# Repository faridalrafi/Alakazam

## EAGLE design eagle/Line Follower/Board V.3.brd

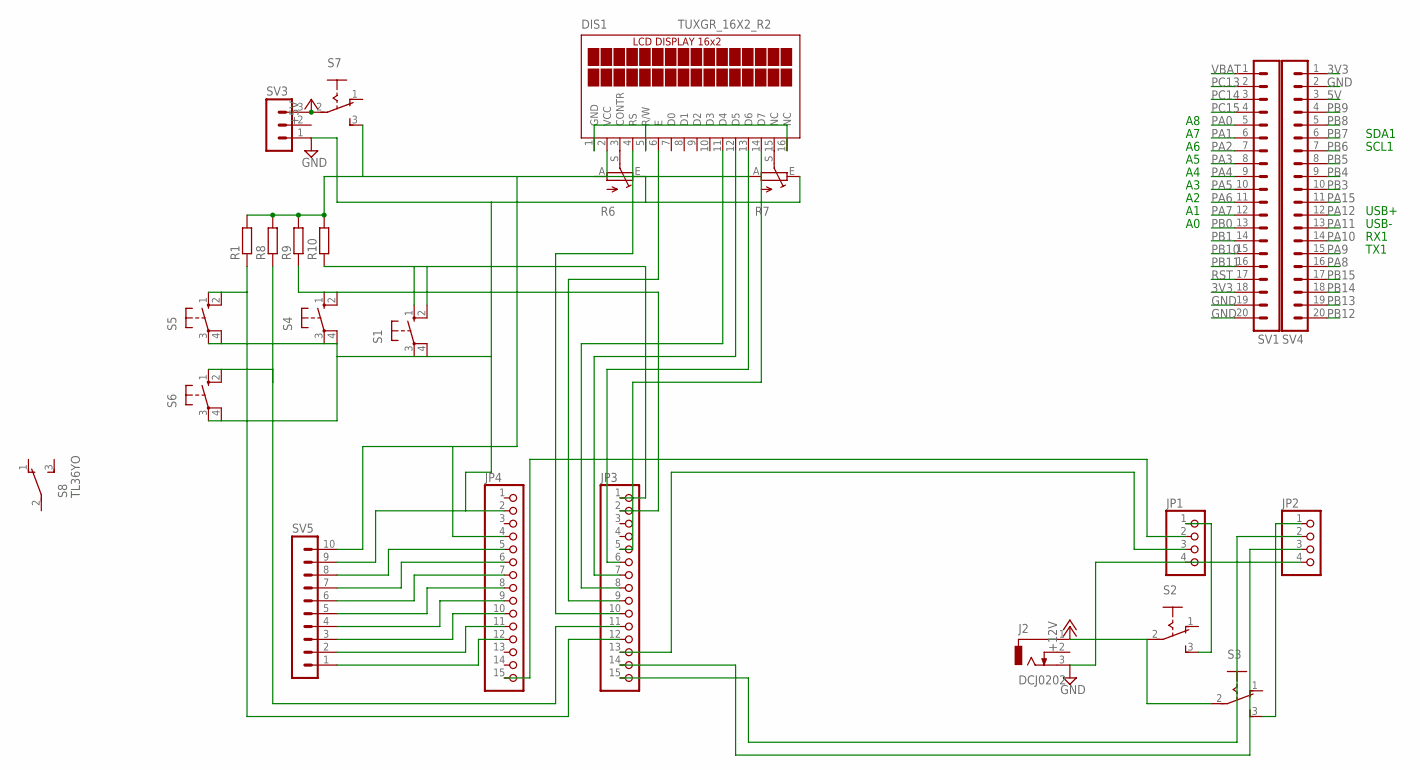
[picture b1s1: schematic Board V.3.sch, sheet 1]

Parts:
DIS1: TUXGR_16X2_R2
J2: DCJ0202
JP1, JP2: PINHD-1X4; 1X04
JP3, JP4: PINHD-1X15; 1X15
R1, R8, R9, R10: R-EU_0204/7; 0204/7
R6, R7: TRIM_EU-B25P; B25P
S1, S4, S5, S6: 10-XX; B3F-10XX
S2, S3, S7: 255SB
S8: TL36YO; TL3XYO
SV1, SV4: MA20-1L
SV3: MA03-1
SV5: MA10-1

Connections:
3V3: SV1.18, SV4.1
5V: SV4.3
+5V: S7.2, SV3.3
+5V2: DIS1.2 (VCC), JP4.4, R1.2, R6.A, R7.A, R8.2, R9.2, R10.2, S7.3 (S), SV5.10
+12V: J2.1, S2.2, S3.2
GND: J2.3, JP1.4, JP2.4, JP4.2, R6.E, R7.E, S1.3, S1.4 (P1), S4.3, S4.4 (P1), S5.3, S5.4 (P1), S6.3, S6.4 (P1), SV1.19, SV1.20, SV3.1, SV4.2, SV5.9
unnamed: JP1.1, S2.3 (S)
unnamed: JP2.1, S3.3 (S)
unnamed: JP3.1, R10.1, S1.1 (S), S1.2 (S1)
unnamed: DIS1.15 (NC), R7.S
unnamed: DIS1.4 (RS), JP3.10
unnamed: DIS1.3 (CONTR), R6.S
unnamed: DIS1.6 (E), JP3.9
unnamed: DIS1.11 (D4), JP3.8
unnamed: JP4.5, SV5.8
unnamed: JP4.6, SV5.7
unnamed: JP4.7, SV5.6
unnamed: JP4.8, SV5.5
unnamed: JP4.9, SV5.4
unnamed: DIS1.12 (D5), JP3.7
unnamed: DIS1.13 (D6), JP3.6
unnamed: DIS1.14 (D7), JP3.5
unnamed: JP3.2, R9.1, S4.1 (S), S4.2 (S1)
unnamed: JP3.11, R8.1, S6.1 (S), S6.2 (S1)
unnamed: JP3.12, R1.1, S5.1 (S), S5.2 (S1)
unnamed: DIS1.1 (GND), DIS1.5 (R/W), DIS1.16 (NC)
unnamed: JP2.3, JP3.14
unnamed: JP4.10, SV5.3
unnamed: JP4.11, SV5.2
unnamed: JP4.12, SV5.1
PA0: SV1.5
PA1: SV1.6
PA2: SV1.7
PA3: SV1.8
PA4: SV1.9
PA5: SV1.10
PA6: SV1.11
PA7: SV1.12
PA8: SV4.16
PA9: SV4.15
PA10: SV4.14
PA11: SV4.13
PA12: SV4.12
PA15: SV4.11
PB0: SV1.13
PB1: SV1.14
PB3: SV4.10
PB4: SV4.9
PB5: SV4.8
PB6: SV4.7
PB7: SV4.6
PB8: SV4.5
PB9: SV4.4
PB10: SV1.15
PB11: SV1.16
PB12: SV4.20
PB13: SV4.19
PB14: SV4.18
PB15: SV4.17
PC13: SV1.2
PC14: SV1.3
PC15: SV1.4
RST: SV1.17
VBAT: SV1.1

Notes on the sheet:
SDA1
SCL1
RX1
TX1
USB-
USB+

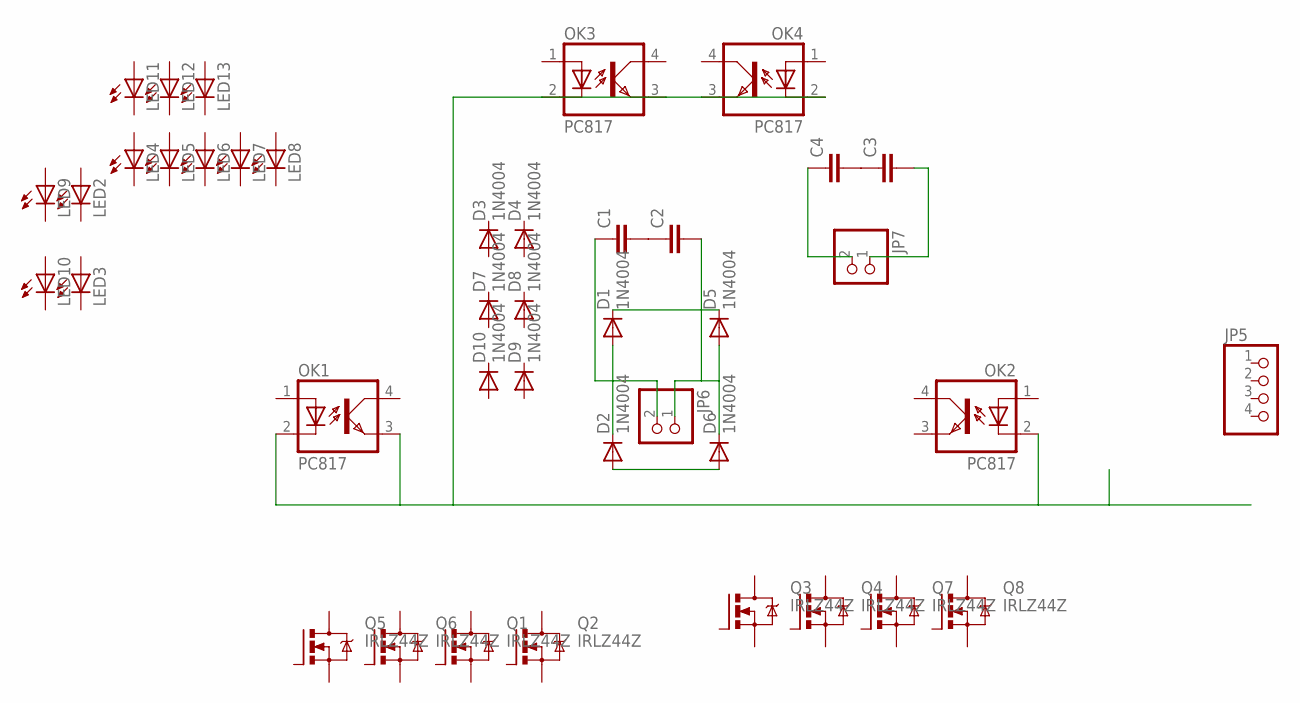
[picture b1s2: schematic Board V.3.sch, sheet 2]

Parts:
C1, C2, C3, C4: C-EU025-025X050; C025-025X050
D1, D2, D3, D4, D5, D6, D7, D8, D9, D10: 1N4004; DO41-10
JP5: PINHD-1X4; 1X04
JP6, JP7: PINHD-1X2/90; 1X02/90
LED2, LED3, LED4, LED5, LED6, LED7, LED8, LED9, LED10, LED11, LED12, LED13: LED5MM
OK1, OK2, OK3, OK4: PC817; DIL04
Q1, Q2, Q3, Q4, Q5, Q6, Q7, Q8: IRLZ44Z; TO220BH

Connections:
+12V1: D1.C, D5.C
GND1: OK1.2 (C), OK1.3 (EMIT), OK2.2 (C), OK3.2 (C), OK3.3 (EMIT), OK4.2 (C), OK4.3 (EMIT)
unnamed: C3.1, C4.2
unnamed: D2.A, D6.A
unnamed: C4.1, JP7.2
unnamed: C1.2, C2.1
unnamed: C1.1, D1.A, D2.C, JP6.2
unnamed: C3.2, JP7.1
unnamed: C2.2, D5.A, D6.C, JP6.1

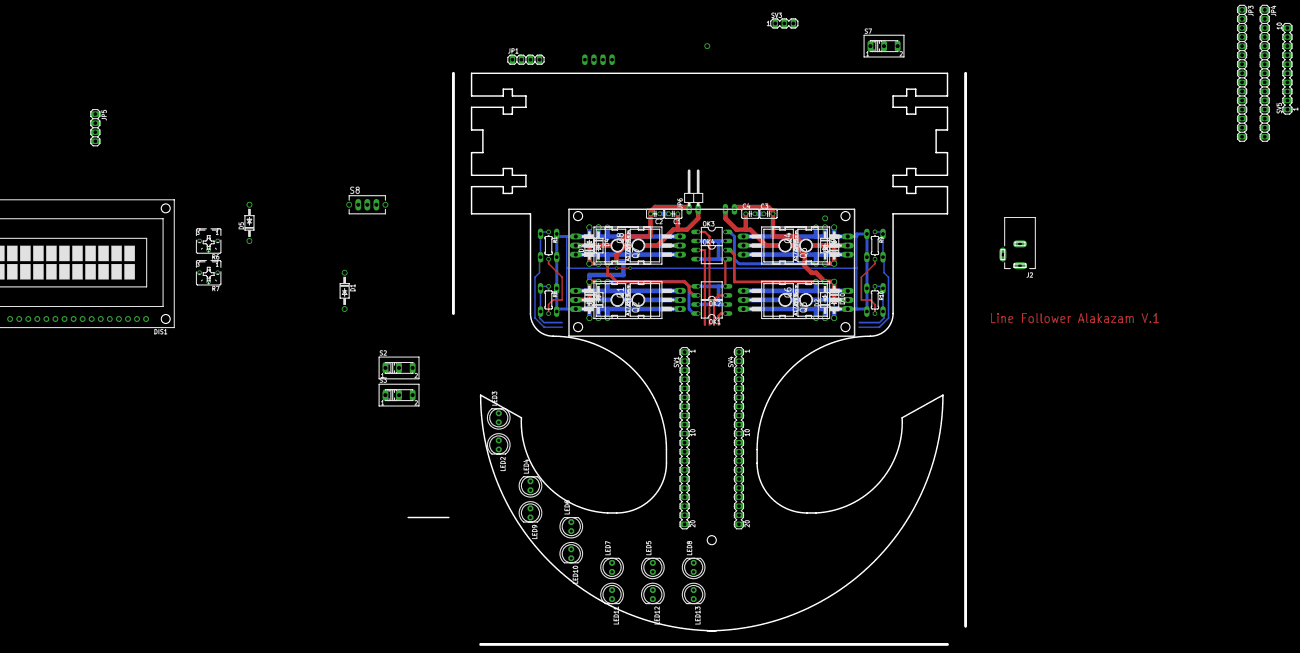
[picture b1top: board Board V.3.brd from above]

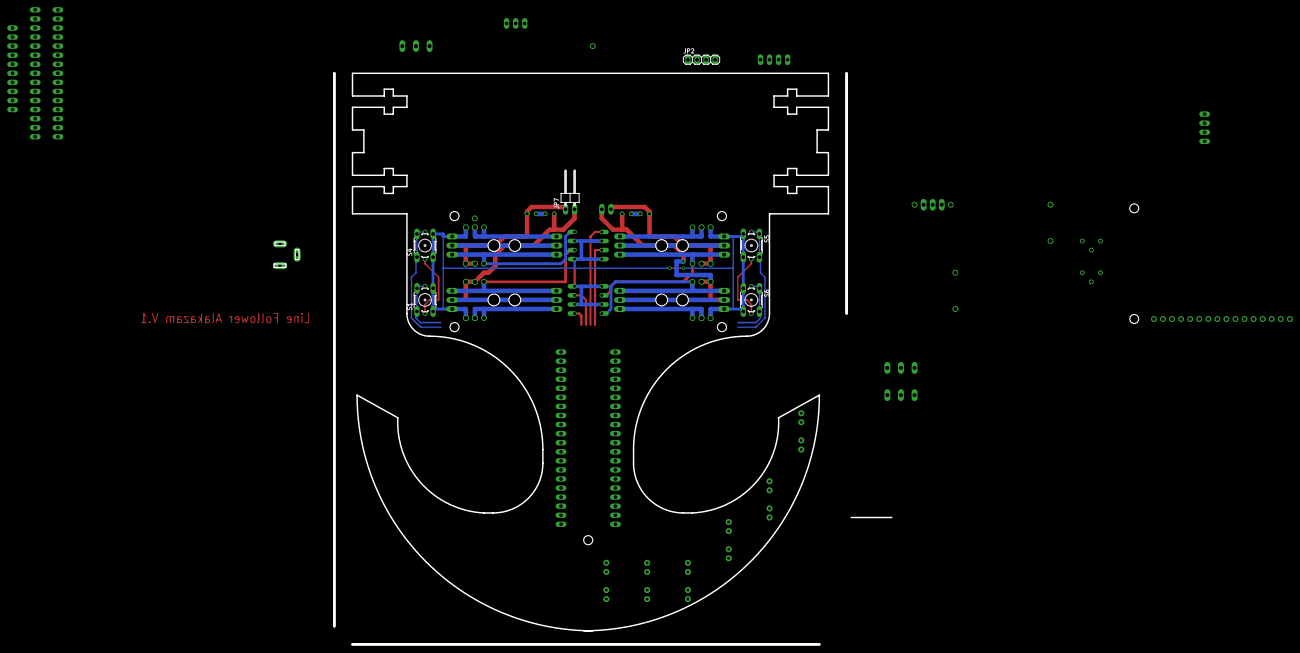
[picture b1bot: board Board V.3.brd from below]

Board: 2 copper layers, 173.1 x 160.0 mm, 65 parts (6 on the bottom side), 38 nets.

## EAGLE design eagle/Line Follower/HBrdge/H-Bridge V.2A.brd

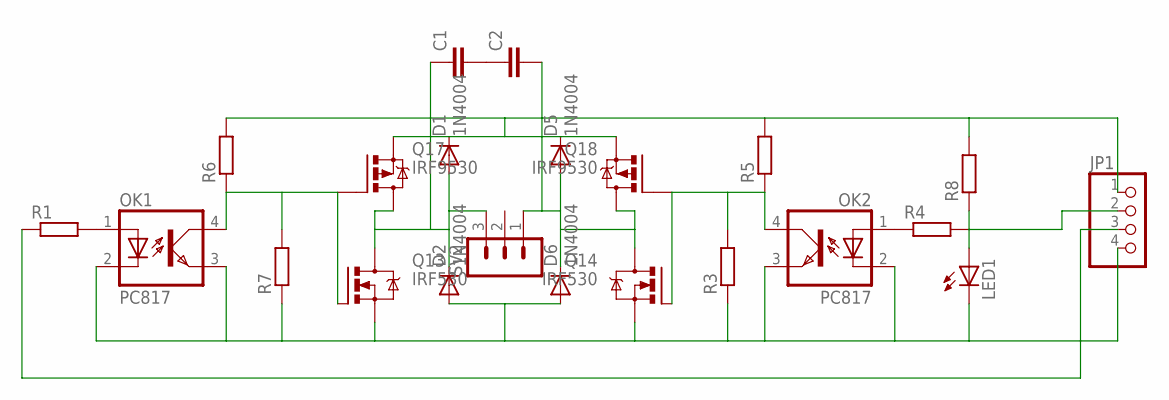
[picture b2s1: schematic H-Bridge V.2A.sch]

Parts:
C1, C2: C-EU025-025X050; C025-025X050
D1, D2, D5, D6: 1N4004; DO41-10
JP1: PINHD-1X4; 1X04
LED1: LED3MM
OK1, OK2: PC817; DIL04
Q13, Q14: IRF530; TO220BV
Q17, Q18: IRF9530; TO220BV
R1, R4, R5, R6, R8: R-EU_0207/10; 0207/10
R3, R7: R-EU_0204/7; 0204/7
SV2: MA03-1

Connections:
+12V: D1.C, D5.C, JP1.1, Q17.S, Q18.S, R5.2, R6.2, R8.2
GND: D2.A, D6.A, JP1.4, LED1.K (C), OK1.2 (C), OK1.3 (EMIT), OK2.2 (C), OK2.3 (EMIT), Q13.S, Q14.S, R3.1, R7.1
unnamed: OK2.1 (A), R4.1
unnamed: OK1.1 (A), R1.2
unnamed: C1.2, C2.1
unnamed: C2.2, D5.A, D6.C, Q14.D, Q18.D, SV2.1
unnamed: C1.1, D1.A, D2.C, Q13.D, Q17.D, SV2.3
unnamed: LED1.A, R8.1
unnamed: OK2.4 (COL), Q14.G, Q18.G, R3.2, R5.1
unnamed: OK1.4 (COL), Q13.G, Q17.G, R6.1, R7.2
PWM1: JP1.2, R4.2
PWM2: JP1.3, R1.1

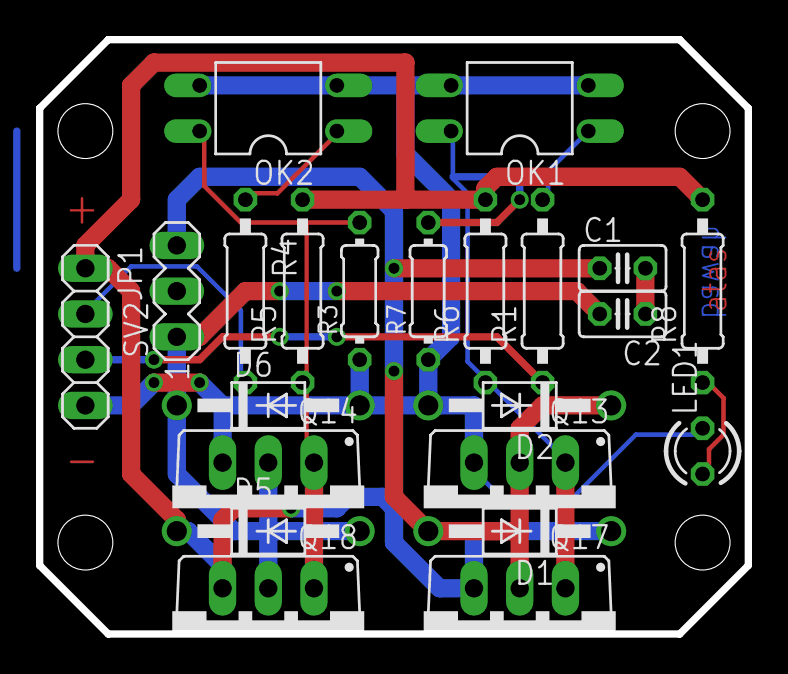
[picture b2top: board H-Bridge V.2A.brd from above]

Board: 2 copper layers, 39.4 x 33.0 mm, 22 parts (0 on the bottom side), 12 nets.

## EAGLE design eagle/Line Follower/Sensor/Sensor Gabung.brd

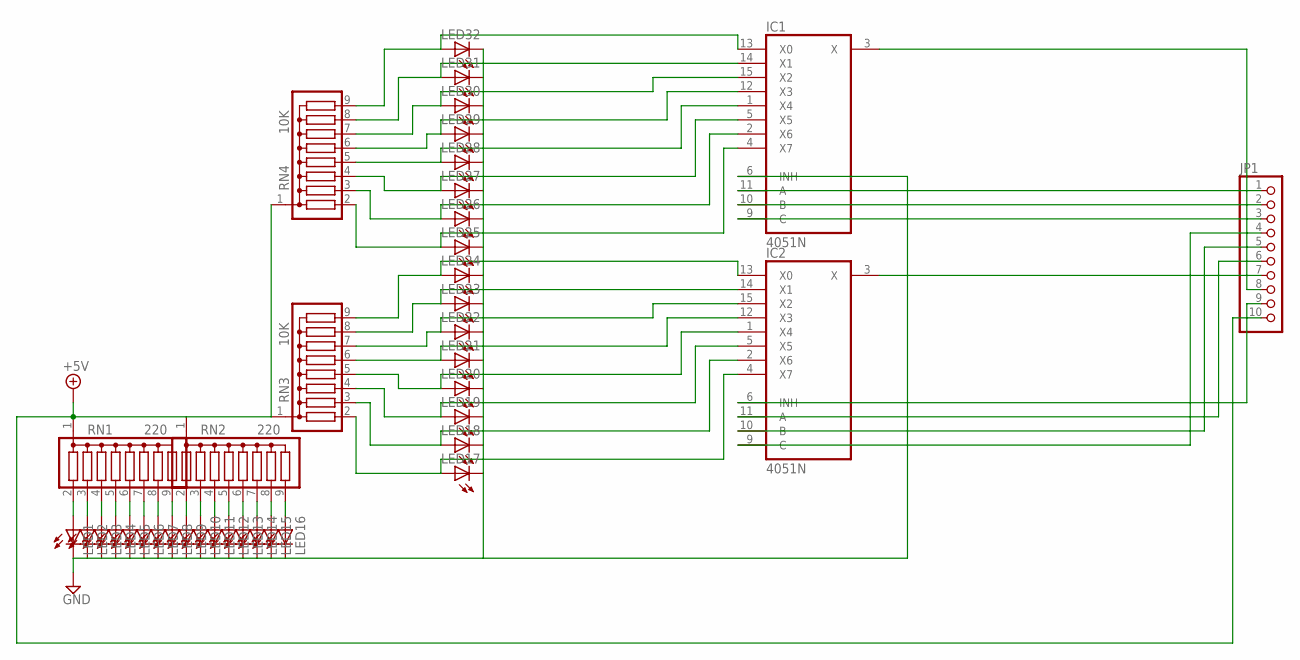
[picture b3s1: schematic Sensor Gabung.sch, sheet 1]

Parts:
IC1, IC2: 4051N; DIL16
JP1: PINHD-1X10; 1X10
LED1, LED2, LED3, LED4, LED5, LED6, LED7, LED8, LED9, LED10, LED11, LED12, LED13, LED14, LED15, LED16, LED17, LED18, LED19, LED20, LED21, LED22, LED23, LED24, LED25, LED26, LED27, LED28, LED29, LED30, LED31, LED32: LED3MM
RN1, RN2: 220; SIL9
RN3, RN4: 10K; SIL9

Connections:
+5V: IC1.16 (VCC), IC2.16 (VCC), JP1.10, RN1.1, RN2.1, RN3.1, RN4.1; also elsewhere on the board
GND: IC1.6 (INH), IC1.8 (GND), IC2.6 (INH), IC2.8 (GND), JP1.9, LED1.K (C), LED2.K (C), LED3.K (C), LED4.K (C), LED5.K (C), LED6.K (C), LED7.K (C), LED8.K (C), LED9.K (C), LED10.K (C), LED11.K (C), LED12.K (C), LED13.K (C), LED14.K (C), LED15.K (C), LED16.K (C), LED17.K (C), LED18.K (C), LED19.K (C), LED20.K (C), LED21.K (C), LED22.K (C), LED23.K (C), LED24.K (C), LED25.K (C), LED26.K (C), LED27.K (C), LED28.K (C), LED29.K (C), LED30.K (C), LED31.K (C), LED32.K (C); also elsewhere on the board
unnamed: IC1.10 (B), JP1.2
unnamed: IC1.9 (C), JP1.3
unnamed: IC2.11 (A), JP1.6
unnamed: IC2.10 (B), JP1.5
unnamed: IC2.9 (C), JP1.4
unnamed: IC2.3 (X), JP1.7
unnamed: LED1.A, RN1.2
unnamed: LED2.A, RN1.3
unnamed: IC2.4 (X7), LED17.A, RN3.2
unnamed: IC2.2 (X6), LED18.A, RN3.3
unnamed: IC2.5 (X5), LED19.A, RN3.4
unnamed: IC2.1 (X4), LED20.A, RN3.5
unnamed: IC2.12 (X3), LED21.A, RN3.6
unnamed: IC2.15 (X2), LED22.A, RN3.7
unnamed: IC2.14 (X1), LED23.A, RN3.8
unnamed: IC2.13 (X0), LED24.A, RN3.9
unnamed: IC1.4 (X7), LED25.A, RN4.2
unnamed: IC1.2 (X6), LED26.A, RN4.3
unnamed: IC1.5 (X5), LED27.A, RN4.4
unnamed: IC1.1 (X4), LED28.A, RN4.5
unnamed: IC1.12 (X3), LED29.A, RN4.6
unnamed: IC1.15 (X2), LED30.A, RN4.7
unnamed: IC1.14 (X1), LED31.A, RN4.8
unnamed: IC1.13 (X0), LED32.A, RN4.9
unnamed: LED3.A, RN1.4
unnamed: LED4.A, RN1.5
unnamed: LED5.A, RN1.6
unnamed: LED6.A, RN1.7
unnamed: LED7.A, RN1.8
unnamed: LED8.A, RN1.9
unnamed: LED9.A, RN2.2
unnamed: LED10.A, RN2.3
unnamed: LED11.A, RN2.4
unnamed: LED12.A, RN2.5
unnamed: LED13.A, RN2.6
unnamed: LED14.A, RN2.7
unnamed: LED15.A, RN2.8
unnamed: LED16.A, RN2.9
unnamed: IC1.3 (X), JP1.8
unnamed: IC1.11 (A), JP1.1
VEE: IC1.7 (VEE), IC2.7 (VEE)

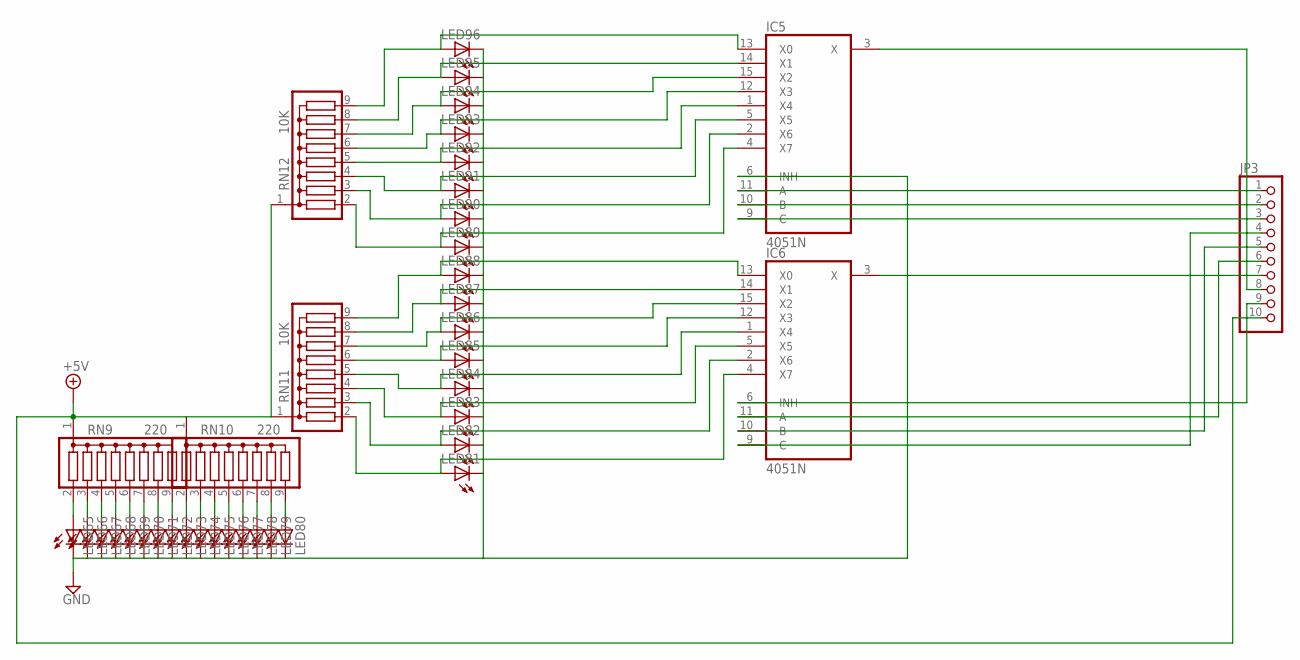
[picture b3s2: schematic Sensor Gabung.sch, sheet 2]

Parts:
IC5, IC6: 4051N; DIL16
JP3: PINHD-1X10; 1X10
LED65, LED66, LED67, LED68, LED69, LED70, LED71, LED72, LED73, LED74, LED75, LED76, LED77, LED78, LED79, LED80, LED81, LED82, LED83, LED84, LED85, LED86, LED87, LED88, LED89, LED90, LED91, LED92, LED93, LED94, LED95, LED96: LED3MM
RN9, RN10: 220; SIL9
RN11, RN12: 10K; SIL9

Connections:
+5V: IC5.16 (VCC), IC6.16 (VCC), JP3.10, RN9.1, RN10.1, RN11.1, RN12.1; also elsewhere on the board
GND: IC5.6 (INH), IC5.7 (VEE), IC5.8 (GND), IC6.6 (INH), IC6.7 (VEE), IC6.8 (GND), JP3.9, LED65.K (C), LED66.K (C), LED67.K (C), LED68.K (C), LED69.K (C), LED70.K (C), LED71.K (C), LED72.K (C), LED73.K (C), LED74.K (C), LED75.K (C), LED76.K (C), LED77.K (C), LED78.K (C), LED79.K (C), LED80.K (C), LED81.K (C), LED82.K (C), LED83.K (C), LED84.K (C), LED85.K (C), LED86.K (C), LED87.K (C), LED88.K (C), LED89.K (C), LED90.K (C), LED91.K (C), LED92.K (C), LED93.K (C), LED94.K (C), LED95.K (C), LED96.K (C); also elsewhere on the board
unnamed: IC6.4 (X7), LED81.A, RN11.2
unnamed: IC6.2 (X6), LED82.A, RN11.3
unnamed: IC6.5 (X5), LED83.A, RN11.4
unnamed: IC6.1 (X4), LED84.A, RN11.5
unnamed: IC6.12 (X3), LED85.A, RN11.6
unnamed: IC6.15 (X2), LED86.A, RN11.7
unnamed: IC6.14 (X1), LED87.A, RN11.8
unnamed: IC6.13 (X0), LED88.A, RN11.9
unnamed: IC5.4 (X7), LED89.A, RN12.2
unnamed: IC5.2 (X6), LED90.A, RN12.3
unnamed: IC5.5 (X5), LED91.A, RN12.4
unnamed: IC5.1 (X4), LED92.A, RN12.5
unnamed: IC5.12 (X3), LED93.A, RN12.6
unnamed: IC5.15 (X2), LED94.A, RN12.7
unnamed: IC5.14 (X1), LED95.A, RN12.8
unnamed: IC5.13 (X0), LED96.A, RN12.9
unnamed: LED65.A, RN9.2
unnamed: LED66.A, RN9.3
unnamed: LED67.A, RN9.4
unnamed: LED68.A, RN9.5
unnamed: LED69.A, RN9.6
unnamed: LED70.A, RN9.7
unnamed: LED71.A, RN9.8
unnamed: LED72.A, RN9.9
unnamed: LED73.A, RN10.2
unnamed: LED74.A, RN10.3
unnamed: LED75.A, RN10.4
unnamed: LED76.A, RN10.5
unnamed: LED77.A, RN10.6
unnamed: LED78.A, RN10.7
unnamed: LED79.A, RN10.8
unnamed: LED80.A, RN10.9
unnamed: IC5.3 (X), JP3.8
unnamed: IC5.11 (A), JP3.1
unnamed: IC5.10 (B), JP3.2
unnamed: IC5.9 (C), JP3.3
unnamed: IC6.11 (A), JP3.6
unnamed: IC6.10 (B), JP3.5
unnamed: IC6.9 (C), JP3.4
unnamed: IC6.3 (X), JP3.7

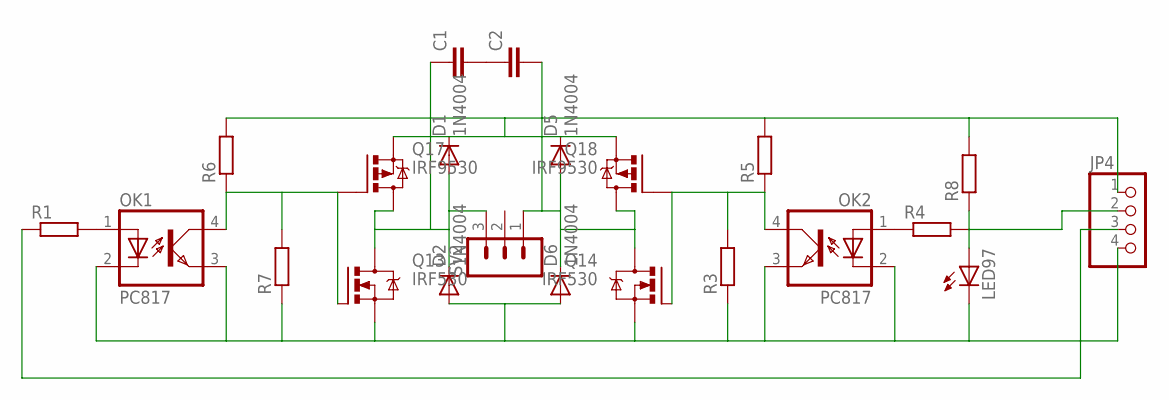
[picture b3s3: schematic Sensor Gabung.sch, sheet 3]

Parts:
C1, C2: C-EU025-025X050; C025-025X050
D1, D2, D5, D6: 1N4004; DO41-10
JP4: PINHD-1X4; 1X04
LED97: LED3MM
OK1, OK2: PC817; DIL04
Q13, Q14: IRF530; TO220BV
Q17, Q18: IRF9530; TO220BV
R1, R4, R5, R6, R8: R-EU_0207/10; 0207/10
R3, R7: R-EU_0204/7; 0204/7
SV2: MA03-1

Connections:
+12V: D1.C, D5.C, JP4.1, Q17.S, Q18.S, R5.2, R6.2, R8.2
GND1: D2.A, D6.A, JP4.4, LED97.K (C), OK1.2 (C), OK1.3 (EMIT), OK2.2 (C), OK2.3 (EMIT), Q13.S, Q14.S, R3.1, R7.1; also elsewhere on the board
unnamed: C2.2, D5.A, D6.C, Q14.D, Q18.D, SV2.1
unnamed: C1.1, D1.A, D2.C, Q13.D, Q17.D, SV2.3
unnamed: OK2.4 (COL), Q14.G, Q18.G, R3.2, R5.1
unnamed: OK1.4 (COL), Q13.G, Q17.G, R6.1, R7.2
unnamed: LED97.A, R8.1
unnamed: OK2.1 (A), R4.1
unnamed: OK1.1 (A), R1.2
unnamed: C1.2, C2.1
PWM1: JP4.2, R4.2
PWM2: JP4.3, R1.1

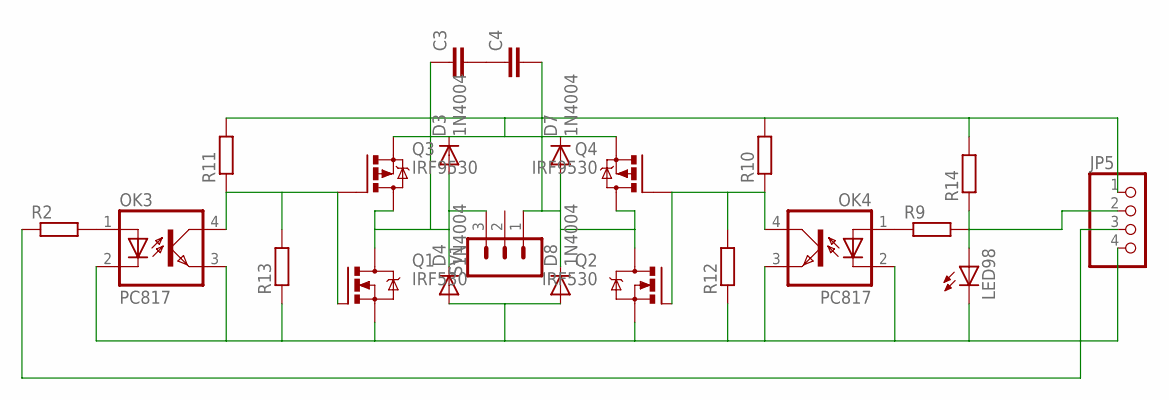
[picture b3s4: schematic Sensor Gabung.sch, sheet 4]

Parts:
C3, C4: C-EU025-025X050; C025-025X050
D3, D4, D7, D8: 1N4004; DO41-10
JP5: PINHD-1X4; 1X04
LED98: LED3MM
OK3, OK4: PC817; DIL04
Q1, Q2: IRF530; TO220BV
Q3, Q4: IRF9530; TO220BV
R2, R9, R10, R11, R14: R-EU_0207/10; 0207/10
R12, R13: R-EU_0204/7; 0204/7
SV1: MA03-1

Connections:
+12V1: D3.C, D7.C, JP5.1, Q3.S, Q4.S, R10.2, R11.2, R14.2
GND2: D4.A, D8.A, JP5.4, LED98.K (C), OK3.2 (C), OK3.3 (EMIT), OK4.2 (C), OK4.3 (EMIT), Q1.S, Q2.S, R12.1, R13.1
unnamed: C4.2, D7.A, D8.C, Q2.D, Q4.D, SV1.1
unnamed: C3.1, D3.A, D4.C, Q1.D, Q3.D, SV1.3
unnamed: OK4.4 (COL), Q2.G, Q4.G, R10.1, R12.2
unnamed: OK3.4 (COL), Q1.G, Q3.G, R11.1, R13.2
unnamed: LED98.A, R14.1
unnamed: OK4.1 (A), R9.1
unnamed: OK3.1 (A), R2.2
unnamed: C3.2, C4.1
PWM3: JP5.3, R2.1
PWM4: JP5.2, R9.2

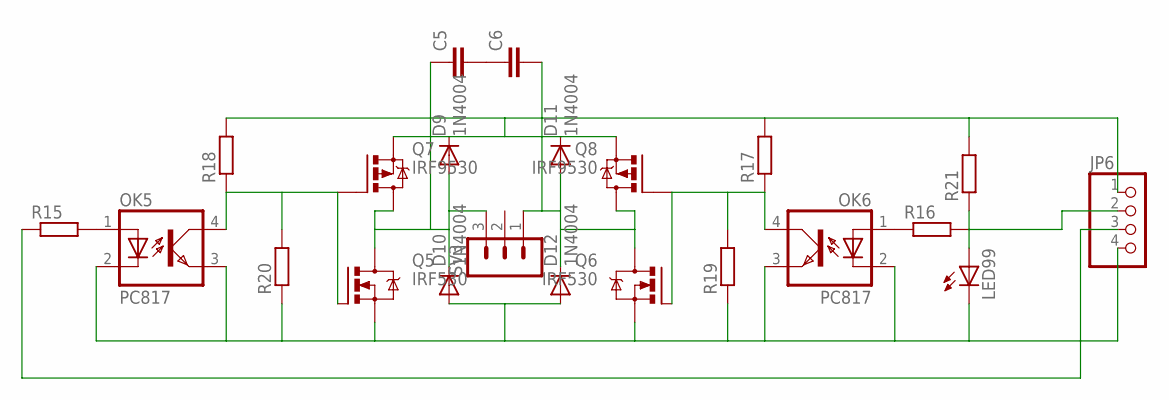
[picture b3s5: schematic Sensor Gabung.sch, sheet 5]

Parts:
C5, C6: C-EU025-025X050; C025-025X050
D9, D10, D11, D12: 1N4004; DO41-10
JP6: PINHD-1X4; 1X04
LED99: LED3MM
OK5, OK6: PC817; DIL04
Q5, Q6: IRF530; TO220BV
Q7, Q8: IRF9530; TO220BV
R15, R16, R17, R18, R21: R-EU_0207/10; 0207/10
R19, R20: R-EU_0204/7; 0204/7
SV3: MA03-1

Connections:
+12V2: D9.C, D11.C, JP6.1, Q7.S, Q8.S, R17.2, R18.2, R21.2
GND3: D10.A, D12.A, JP6.4, LED99.K (C), OK5.2 (C), OK5.3 (EMIT), OK6.2 (C), OK6.3 (EMIT), Q5.S, Q6.S, R19.1, R20.1
unnamed: C6.2, D11.A, D12.C, Q6.D, Q8.D, SV3.1
unnamed: C5.1, D9.A, D10.C, Q5.D, Q7.D, SV3.3
unnamed: OK6.4 (COL), Q6.G, Q8.G, R17.1, R19.2
unnamed: OK5.4 (COL), Q5.G, Q7.G, R18.1, R20.2
unnamed: LED99.A, R21.1
unnamed: OK6.1 (A), R16.1
unnamed: OK5.1 (A), R15.2
unnamed: C5.2, C6.1
PWM5: JP6.3, R15.1
PWM6: JP6.2, R16.2

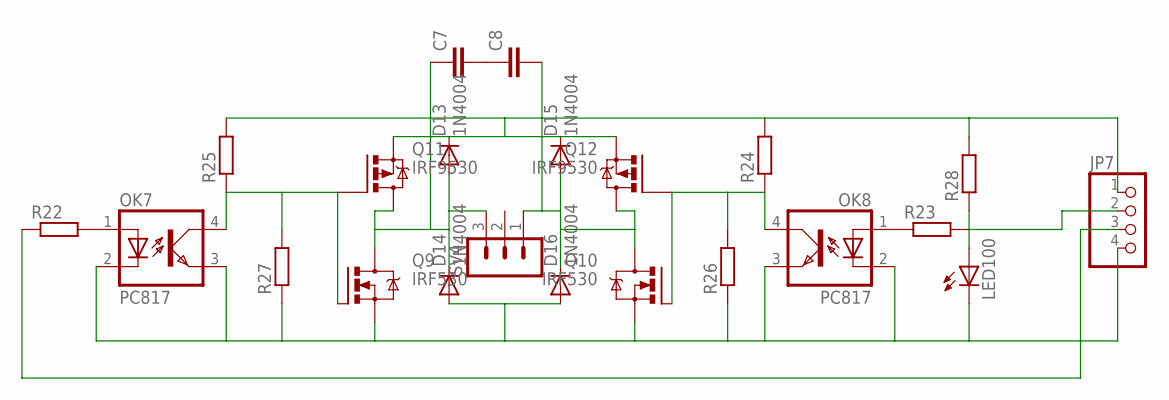
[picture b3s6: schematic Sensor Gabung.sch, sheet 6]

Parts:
C7, C8: C-EU025-025X050; C025-025X050
D13, D14, D15, D16: 1N4004; DO41-10
JP7: PINHD-1X4; 1X04
LED100: LED3MM
OK7, OK8: PC817; DIL04
Q9, Q10: IRF530; TO220BV
Q11, Q12: IRF9530; TO220BV
R22, R23, R24, R25, R28: R-EU_0207/10; 0207/10
R26, R27: R-EU_0204/7; 0204/7
SV4: MA03-1

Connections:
+12V3: D13.C, D15.C, JP7.1, Q11.S, Q12.S, R24.2, R25.2, R28.2
GND4: D14.A, D16.A, JP7.4, LED100.K (C), OK7.2 (C), OK7.3 (EMIT), OK8.2 (C), OK8.3 (EMIT), Q9.S, Q10.S, R26.1, R27.1
unnamed: C8.2, D15.A, D16.C, Q10.D, Q12.D, SV4.1
unnamed: C7.1, D13.A, D14.C, Q9.D, Q11.D, SV4.3
unnamed: OK8.4 (COL), Q10.G, Q12.G, R24.1, R26.2
unnamed: OK7.4 (COL), Q9.G, Q11.G, R25.1, R27.2
unnamed: LED100.A, R28.1
unnamed: OK8.1 (A), R23.1
unnamed: OK7.1 (A), R22.2
unnamed: C7.2, C8.1
PWM7: JP7.3, R22.1
PWM8: JP7.2, R23.2

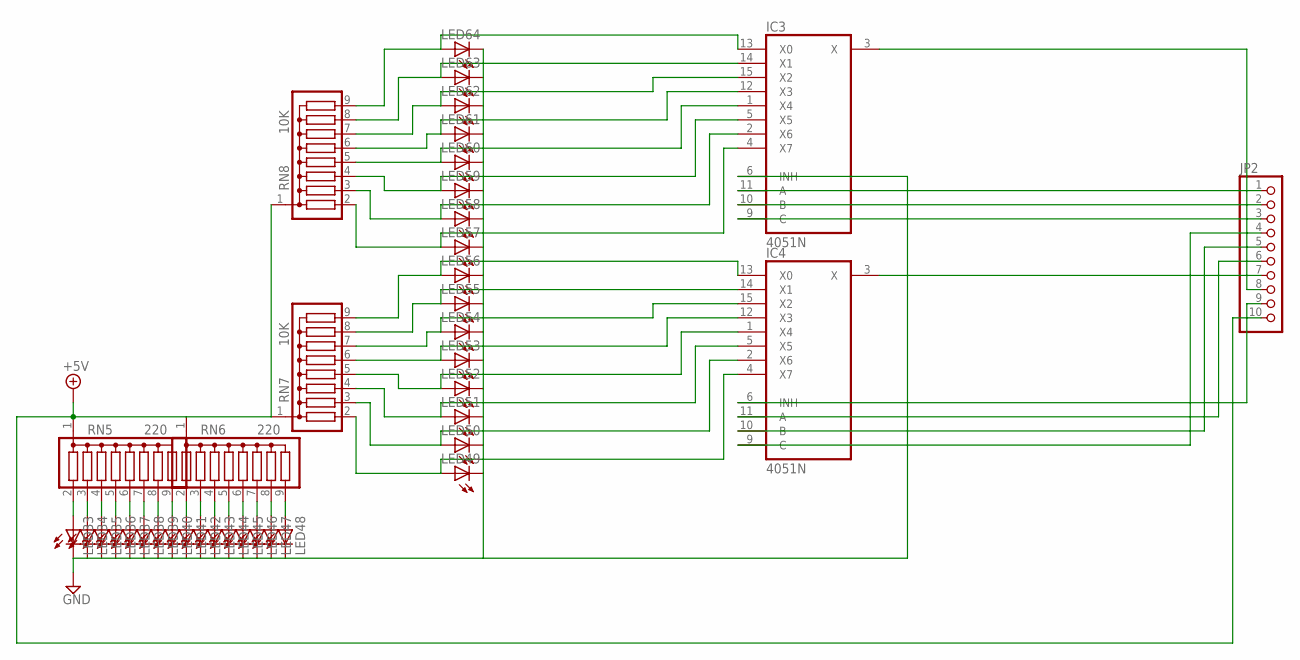
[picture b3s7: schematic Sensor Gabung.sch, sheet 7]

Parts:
IC3, IC4: 4051N; DIL16
JP2: PINHD-1X10; 1X10
LED33, LED34, LED35, LED36, LED37, LED38, LED39, LED40, LED41, LED42, LED43, LED44, LED45, LED46, LED47, LED48, LED49, LED50, LED51, LED52, LED53, LED54, LED55, LED56, LED57, LED58, LED59, LED60, LED61, LED62, LED63, LED64: LED3MM
RN5, RN6: 220; SIL9
RN7, RN8: 10K; SIL9

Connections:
+5V: IC3.16 (VCC), IC4.16 (VCC), JP2.10, RN5.1, RN6.1, RN7.1, RN8.1; also elsewhere on the board
GND: IC3.6 (INH), IC3.7 (VEE), IC3.8 (GND), IC4.6 (INH), IC4.7 (VEE), IC4.8 (GND), JP2.9, LED33.K (C), LED34.K (C), LED35.K (C), LED36.K (C), LED37.K (C), LED38.K (C), LED39.K (C), LED40.K (C), LED41.K (C), LED42.K (C), LED43.K (C), LED44.K (C), LED45.K (C), LED46.K (C), LED47.K (C), LED48.K (C), LED49.K (C), LED50.K (C), LED51.K (C), LED52.K (C), LED53.K (C), LED54.K (C), LED55.K (C), LED56.K (C), LED57.K (C), LED58.K (C), LED59.K (C), LED60.K (C), LED61.K (C), LED62.K (C), LED63.K (C), LED64.K (C); also elsewhere on the board
unnamed: IC4.4 (X7), LED49.A, RN7.2
unnamed: IC4.2 (X6), LED50.A, RN7.3
unnamed: IC4.5 (X5), LED51.A, RN7.4
unnamed: IC4.1 (X4), LED52.A, RN7.5
unnamed: IC4.12 (X3), LED53.A, RN7.6
unnamed: IC4.15 (X2), LED54.A, RN7.7
unnamed: IC4.14 (X1), LED55.A, RN7.8
unnamed: IC4.13 (X0), LED56.A, RN7.9
unnamed: IC3.4 (X7), LED57.A, RN8.2
unnamed: IC3.2 (X6), LED58.A, RN8.3
unnamed: IC3.5 (X5), LED59.A, RN8.4
unnamed: IC3.1 (X4), LED60.A, RN8.5
unnamed: IC3.12 (X3), LED61.A, RN8.6
unnamed: IC3.15 (X2), LED62.A, RN8.7
unnamed: IC3.14 (X1), LED63.A, RN8.8
unnamed: IC3.13 (X0), LED64.A, RN8.9
unnamed: LED33.A, RN5.2
unnamed: LED34.A, RN5.3
unnamed: LED35.A, RN5.4
unnamed: LED36.A, RN5.5
unnamed: LED37.A, RN5.6
unnamed: LED38.A, RN5.7
unnamed: LED39.A, RN5.8
unnamed: LED40.A, RN5.9
unnamed: LED41.A, RN6.2
unnamed: LED42.A, RN6.3
unnamed: LED43.A, RN6.4
unnamed: LED44.A, RN6.5
unnamed: LED45.A, RN6.6
unnamed: LED46.A, RN6.7
unnamed: LED47.A, RN6.8
unnamed: LED48.A, RN6.9
unnamed: IC3.3 (X), JP2.8
unnamed: IC3.11 (A), JP2.1
unnamed: IC3.10 (B), JP2.2
unnamed: IC3.9 (C), JP2.3
unnamed: IC4.11 (A), JP2.6
unnamed: IC4.10 (B), JP2.5
unnamed: IC4.9 (C), JP2.4
unnamed: IC4.3 (X), JP2.7

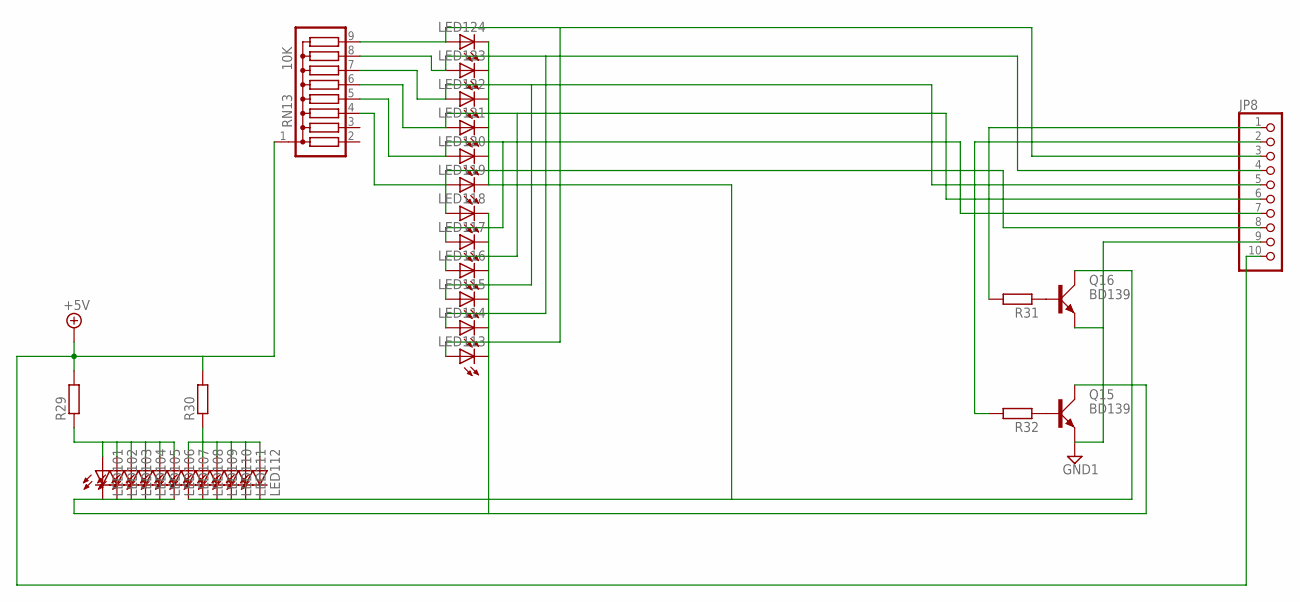
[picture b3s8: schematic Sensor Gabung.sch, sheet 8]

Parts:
JP8: PINHD-1X10; 1X10
LED101, LED102, LED103, LED104, LED105, LED106, LED107, LED108, LED109, LED110, LED111, LED112, LED113, LED114, LED115, LED116, LED117, LED118, LED119, LED120, LED121, LED122, LED123, LED124: LED3MM
Q15, Q16: BD139; TO126AV
R29, R30, R31, R32: R-EU_0207/10; 0207/10
RN13: 10K; SIL9

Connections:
+5V: JP8.10, R29.2, R30.2, RN13.1; also elsewhere on the board
GND1: JP8.9, Q15.E, Q16.E; also elsewhere on the board
unnamed: LED101.A, LED102.A, LED103.A, LED104.A, LED105.A, LED106.A, R29.1
unnamed: LED107.A, LED108.A, LED109.A, LED110.A, LED111.A, LED112.A, R30.1
unnamed: JP8.8, LED118.A, LED119.A, RN13.4
unnamed: JP8.6, LED116.A, LED121.A, RN13.6
unnamed: JP8.5, LED115.A, LED122.A, RN13.7
unnamed: JP8.4, LED114.A, LED123.A, RN13.8
unnamed: JP8.3, LED113.A, LED124.A, RN13.9
unnamed: LED107.K (C), LED108.K (C), LED109.K (C), LED110.K (C), LED111.K (C), LED112.K (C), LED119.K (C), LED120.K (C), LED121.K (C), LED122.K (C), LED123.K (C), LED124.K (C), Q16.C
unnamed: LED101.K (C), LED102.K (C), LED103.K (C), LED104.K (C), LED105.K (C), LED106.K (C), LED113.K (C), LED114.K (C), LED115.K (C), LED116.K (C), LED117.K (C), LED118.K (C), Q15.C
unnamed: Q16.B, R31.1
unnamed: Q15.B, R32.1
unnamed: JP8.1, R31.2
unnamed: JP8.2, R32.2
unnamed: JP8.7, LED117.A, LED120.A, RN13.5

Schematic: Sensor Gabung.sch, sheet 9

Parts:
JP9: PINHD-1X10; 1X10
LED125, LED126, LED127, LED128, LED129, LED130, LED131, LED132, LED133, LED134, LED135, LED136, LED137, LED138, LED139, LED140, LED141, LED142, LED143, LED144, LED145, LED146, LED147, LED148: LED3MM
Q19, Q20: BD139; TO126AV
R33, R34, R35, R36: R-EU_0204/7; 0204/7
RN14: 10K; SIL9

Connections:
+5V: JP9.10, R33.2, R34.2, RN14.1; also elsewhere on the board
GND: JP9.9, Q19.E, Q20.E; also elsewhere on the board
unnamed: LED125.A, LED126.A, LED127.A, LED128.A, LED129.A, LED130.A, R33.1
unnamed: JP9.7, LED141.A, LED144.A, RN14.3
unnamed: JP9.6, LED140.A, LED145.A, RN14.4
unnamed: JP9.5, LED139.A, LED146.A, RN14.5
unnamed: JP9.4, LED138.A, LED147.A, RN14.6
unnamed: JP9.3, LED137.A, LED148.A, RN14.7
unnamed: LED131.A, LED132.A, LED133.A, LED134.A, LED135.A, LED136.A, R34.1
unnamed: LED131.K (C), LED132.K (C), LED133.K (C), LED134.K (C), LED135.K (C), LED136.K (C), LED143.K (C), LED144.K (C), LED145.K (C), LED146.K (C), LED147.K (C), LED148.K (C), Q20.C
unnamed: LED125.K (C), LED126.K (C), LED127.K (C), LED128.K (C), LED129.K (C), LED130.K (C), LED137.K (C), LED138.K (C), LED139.K (C), LED140.K (C), LED141.K (C), LED142.K (C), Q19.C
unnamed: JP9.8, LED142.A, LED143.A, RN14.2
unnamed: Q20.B, R36.1
unnamed: JP9.2, R36.2
unnamed: JP9.1, R35.2
unnamed: Q19.B, R35.1

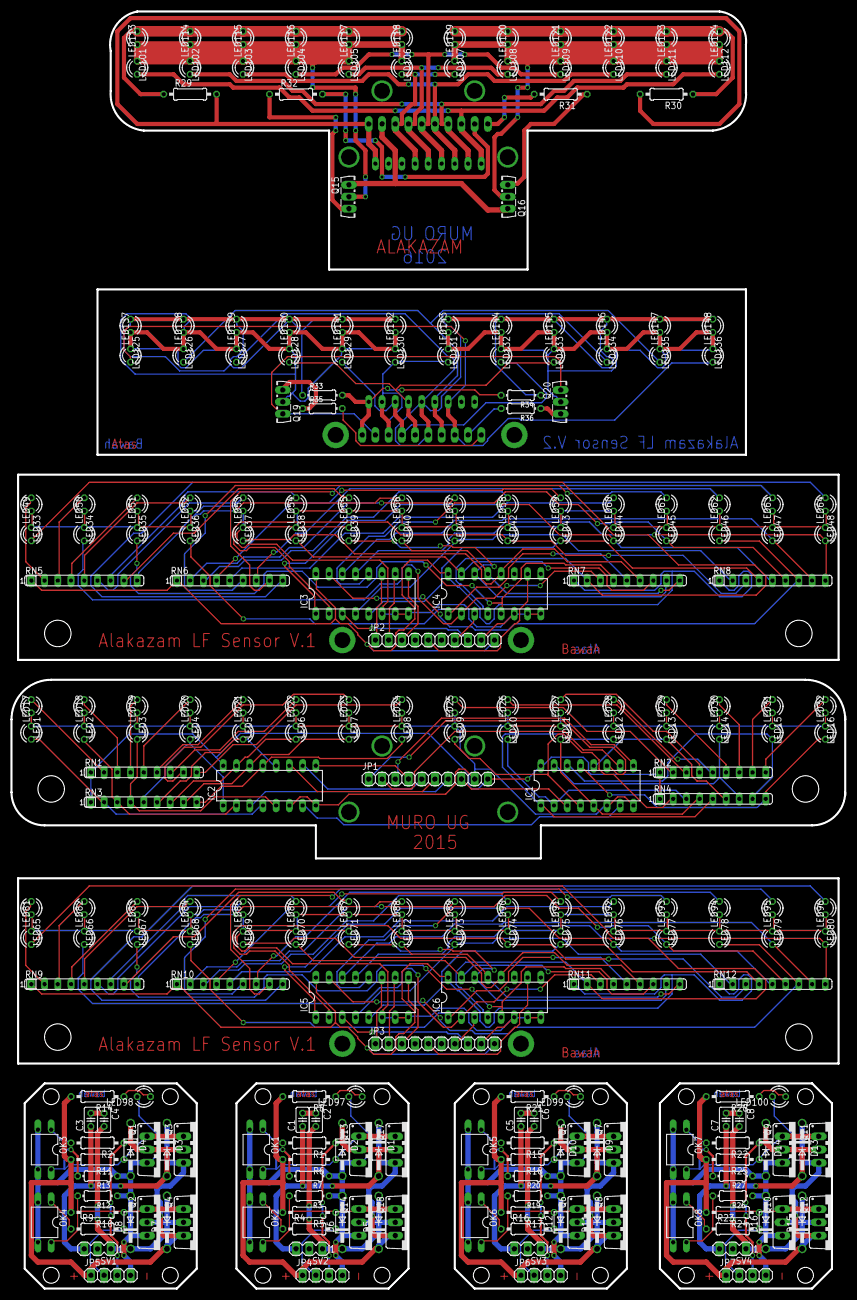
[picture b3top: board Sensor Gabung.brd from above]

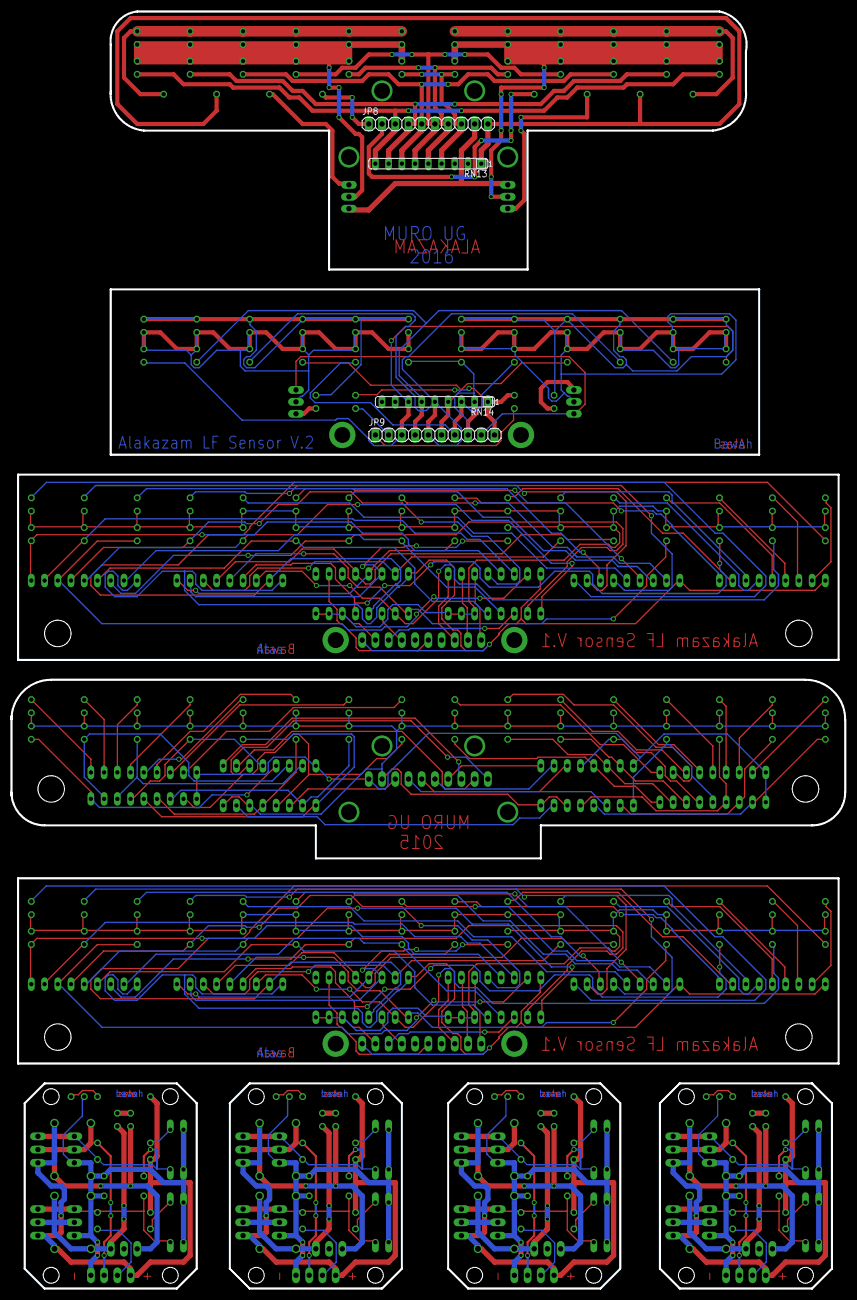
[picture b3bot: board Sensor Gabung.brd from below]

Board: 2 copper layers, 160.0 x 245.1 mm, 269 parts (4 on the bottom side), 199 nets.
